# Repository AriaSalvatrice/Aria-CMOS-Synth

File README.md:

# Aria Salvatrice's WIP CMOS Synth

This repository aims to document the Lunetta-style modular CMOS synth I'm building to learn more about electronics. 

Wanna see it in action?

For now, this stuff is only provided publicly to solicit feedback. Depending on the quality of the completed synth and community interest, maybe I'll turn it into a proper open hardware project fit for human consumption one day. But for now, nobody should reproduce those builds, nor even attempt to learn something from them. I literally didn't know how to make a LED emit light rather than smoke at the start of 2022. I have no clue what I'm doing.

Software you need to open the source files I'm sharing:
- Schematics use [KiCad](https://www.kicad.org/) 6.99+
- Layouts use [DIY Layout Creator](http://diy-fever.com/software/diylc/)
- 3D prints use [FreeCAD](https://www.freecadweb.org/)

Other than this file repository, I document my build process [in a thread on the Look Mum No Computer forum](https://lookmumnocomputer.discourse.group/t/starting-a-little-cmos-synth-build/5375/), post the infrequent video [on my Youtube](https://www.youtube.com/c/AriaSalvatrice), sometimes lurk [/r/synthdiy](https://old.reddit.com/r/synthdiy/), and spam [excessively detailed updates in between the gay shitposts on my personal Tweeter that nobody should follow](https://twitter.com/AriaSalvatrice). 

## About Lunetta and CMOS synths

CMOS synths primarily focus primarily on exploring the interactions of the CMOS 4000 series of chips, which deal with digital logic, signals that are either high or low. Compared to more advanced synth DIY endeavors, they are rather easy to build and understand, cheap to make, and reward experimentation. They are sometimes named after [Stanley Lunetta](http://moosack.net/), who pioneered this style of circuit, and called his work _sound sculptures_. 

Your best introduction to musical applications of CMOS chips would be [Elliot Williams' Logic Noise series](https://hackaday.com/series_of_posts/logic-noise/). To dig deeper, explore over a decade of archives in the [Lunetta forums on electro-music.com](https://electro-music.com/forum/forum-160.html), and read the in-depth circuit analyses of the [Castle Rocktronics](http://castlerocktronics.com/modular.html) modules. 

## Design Goals

Mostly learning electronics for myself, and ending up with a neat little rhythm machine, for now. But it'd be cool if I could eventually turn the best circuits into multiple dedicated PCBs, that you could wire up either with pin headers, or cables going to banana jacks on a panel for a more traditional Lunetta setup.

## Electrical Design

All the guts of the synth are exposed as bare PCBs with male header pins, that the performer patches with female DuPont cables. The small size makes it unsuited for live patching, but exceptionally well suited to experimentation with breadboards.

As there are no panels, the aesthetics of the PCBs are important. When performing on video, they must provide a fun and colorful visual spectacle with mucho Blinkenlichten. They must also double as a reasonably ergonomic user interface.

The system runs on +12V DC. It will also work on +9V, but the values are tuned for +12V, so pitches and envelopes are different at +9V. Some of the circuits I made no longer seem to work at +5V. I picked +12V to make it easier to integrate to a modular synth in the future. There is no dedicated power module yet, it runs off a bench PSU.

To keep the patches readable for the performer, most of the hardwiring is run below the boards. 

Most of the circuits used were designed by much more competent people and shared under permissive terms. Individual credits are provided for each module. If you want to learn, learn from the originals, not from my stuff.

## Mechanical Design

The modules are currently printed with PLA. The models were made with FreeCAD. As I don't know FreeCAD well, they are not as easy to modify as I like and can require some post-processing in Blender, the main value of the FreeCAD project is to have a set of measurements that works pretty well. 

The modules tile to an approximate 60×60mm grid. This allows integrating 100×100mm PCBs in 120×120mm modules comfortably, the maximum size for which some PCB fab houses cut you a special deal for minimum quantity orders.

The modules are held together by their feet with little holding rings that look like buttons, taking countersunk screws. The holes in the feet of modules are reinforced with heat set inserts.

The models should not require a particularly well tuned printer to make. Most can be printed without supports and don't require much post-processing.

Here's the main measurements (will add more as I confirm them precisely):

| Dimension Name | Value | Comments |
|----------------|-------|----------|
| Grid size | 60 × 60 mm 
| Height of modules | 18 mm | Tall enough for vertical headers below the boards, but angled are preferred.
| Spacing between modules | 0.8 mm | Currently, 120×120mm modules don't account for this properly.

## Licensing

lol

-----------

Thanxx for peeping my project. Feel free to look at my learning process, but do not treat my schematics and layouts as instructions yielding an usable product.

Send me thoughts and dog gifs to <woof@aria.dog>.

ttyl,

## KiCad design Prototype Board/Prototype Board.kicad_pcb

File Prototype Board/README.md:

Protoboard Rev2B
----------------

Inspired by commercialy available Permanent Prototype boards, and [Analog Output's Protoboard for Eurorack and Kosmo](https://github.com/holmesrichards/Protoboard). It's 99×99 mm, to get the best deal from PCB fab houses.

There's built-in reverse voltage protection, a status LED, a main decoupling capacitor, room for 6 potentiometers or tactile buttons, and two half-breadboard layouts stacked over each other, with power rails.

The footprints at the bottom can be populated with pushbuttons or potentiometers. They are not connected to the rest of the circuit, but the topmost pad of each group can be used to run wires. Bear in mind that potentiometers are mounted with the pins in reverse order.

The 2 groups of 12 pins at the top and 2 groups of 4 pins on the sides are not connected to anything either. Use them creatively, for example for I/O.

The [W], [X], [Y] and [Z] rows are comprised of 6 groups of 5 pads each, which could be useful to run a signal below a chip.

Those boards are for a single rail power supply, limiting their usefulness for most synthesizer projects.

These are the files for Rev2B. Rev2A has been sent to fabricate (will update). Rev2B is the same with a minor correction (misaligned tracks) and has not been tested.

This is a picture of Rev1, which has a few flaws (such as the status LED shorting if populated). It was my first PCB ever, so I'm happy it even worked at all.

------

_This repository documents my learning process. I advise against building those circuits or learning from them. See the [main README file](../README.md) for more information._

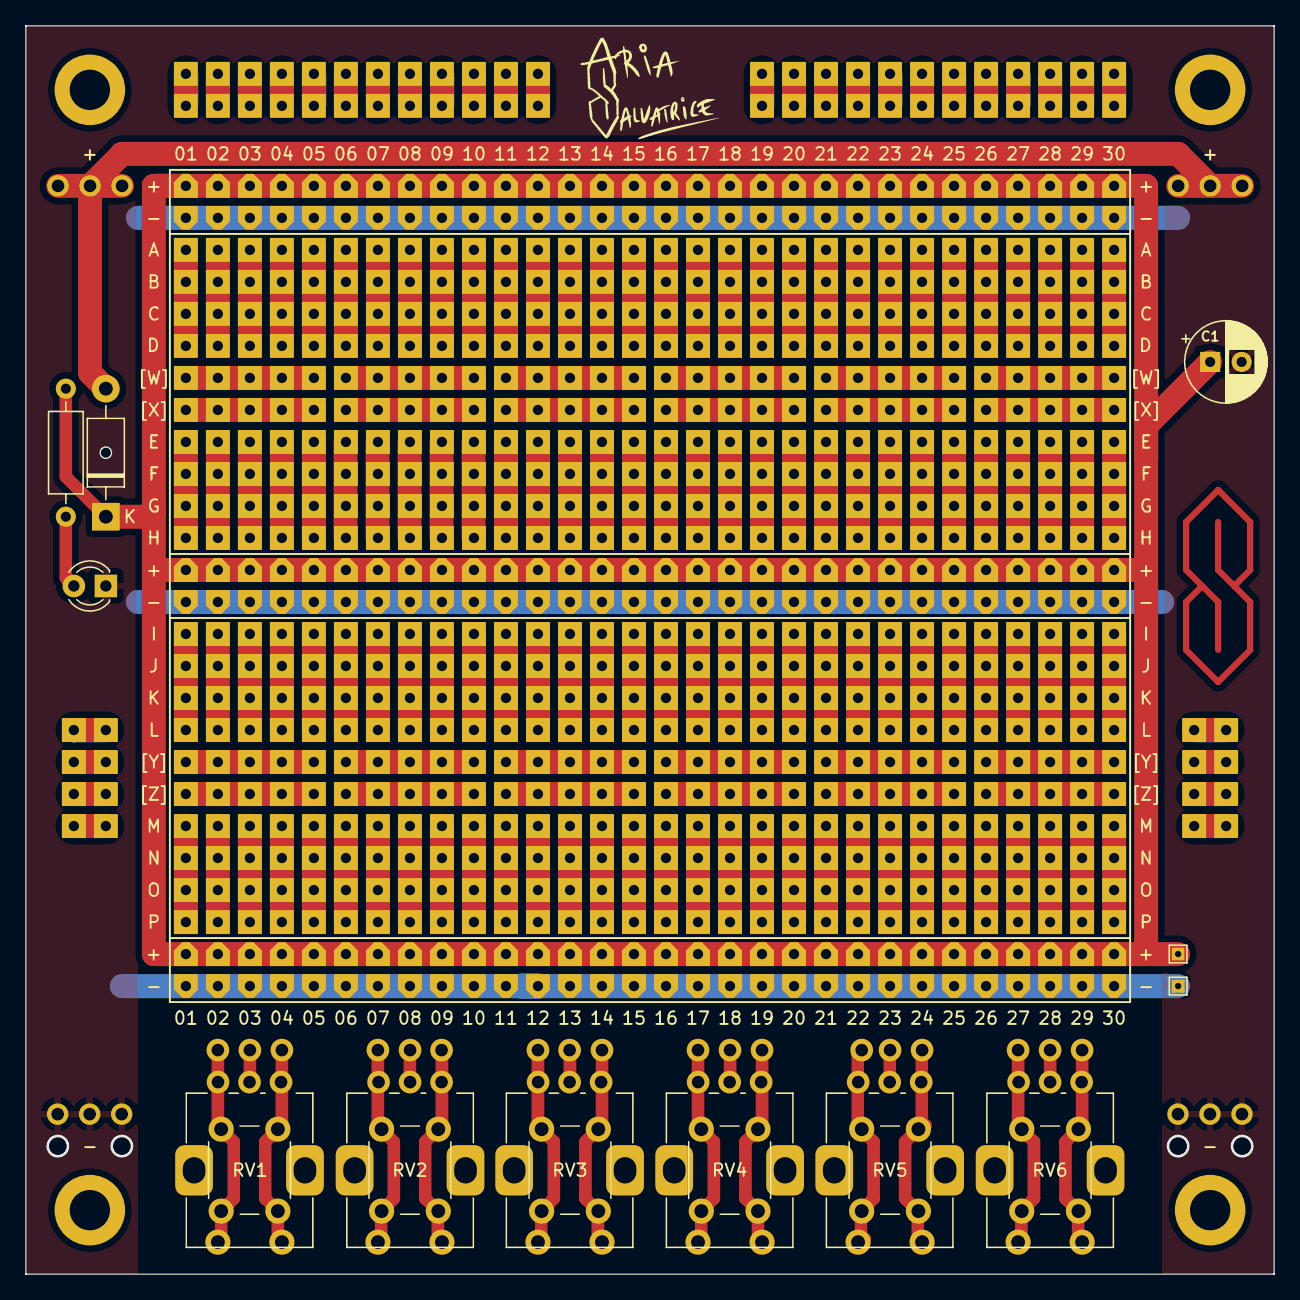
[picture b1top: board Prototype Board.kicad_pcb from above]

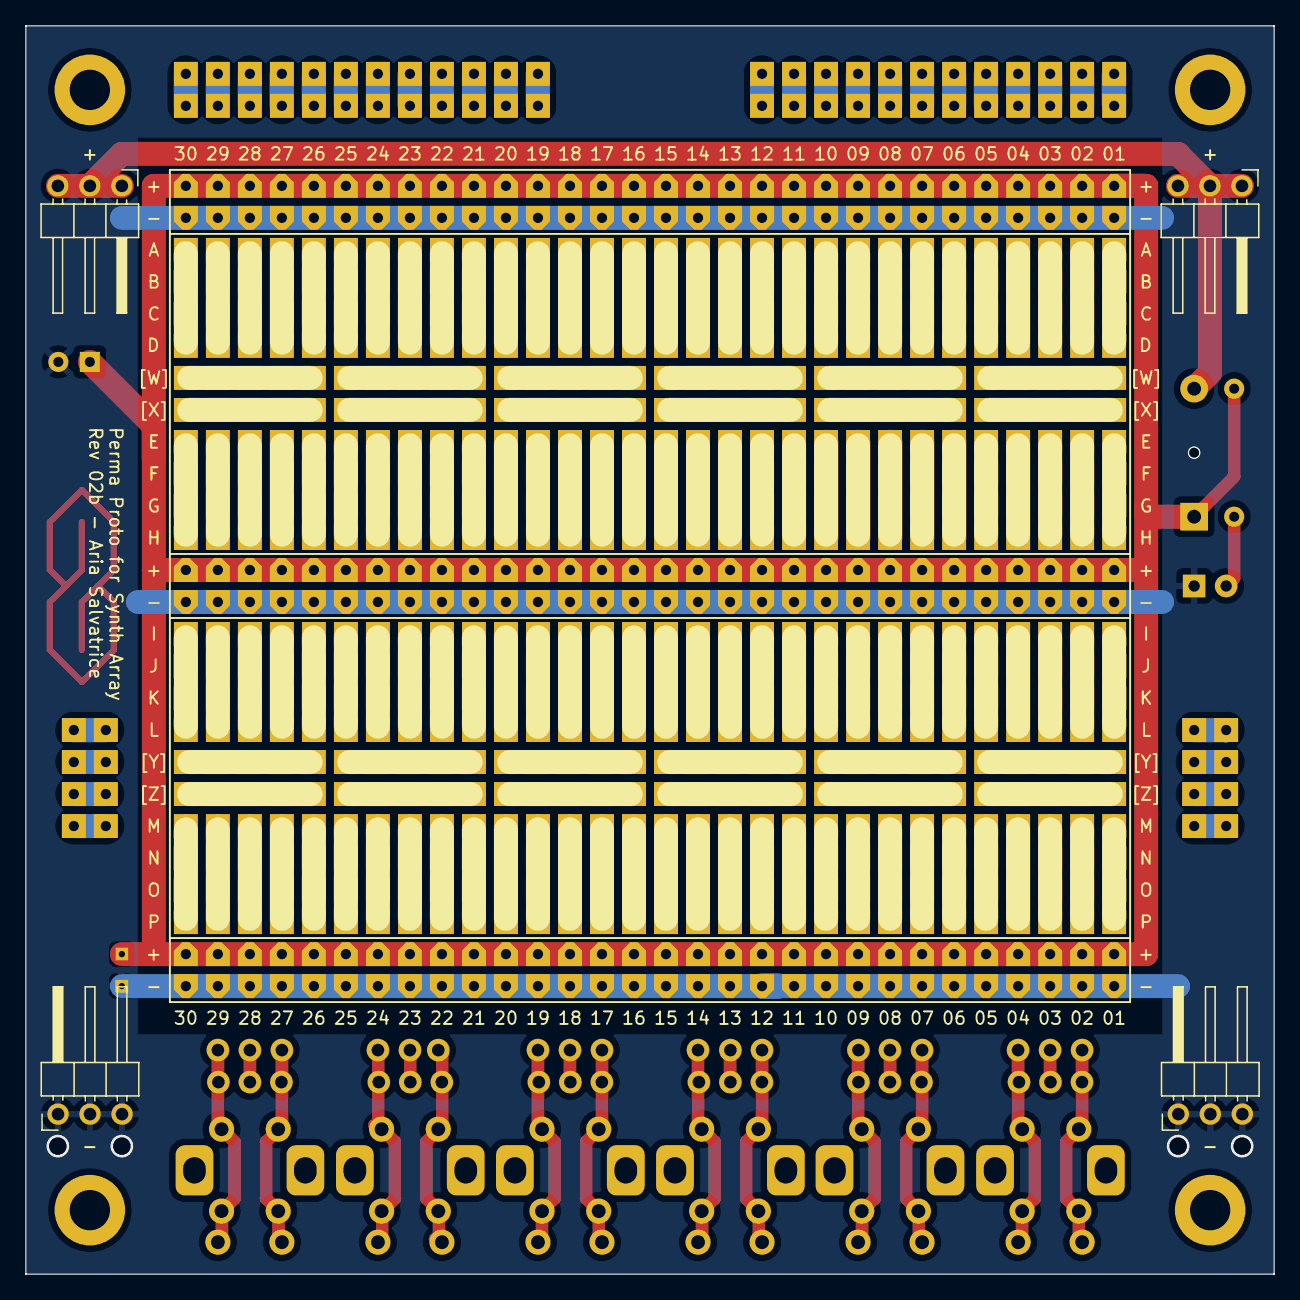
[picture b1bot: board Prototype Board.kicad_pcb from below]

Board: 2 copper layers, 99.1 x 99.1 mm, 219 parts (4 on the bottom side), 22 nets.

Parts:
C1: CP; CP_Radial_D6.3mm_P2.50mm
D1: 1N5817; D_DO-41_SOD81_P10.16mm_Horizontal
D2: LED; LED_D3.0mm
J1, J2, J3, J4, J5, J6, J16, J25, J30, J35, J42, J47, J56, J61, J62, J73, J86, J91, J98, J103, J112, J113, J124, J129, J134, J139, J146, J151, J152, J153, J154, J159: Connectable_Pad_Group_01x02
J7, J8, J9, J10, J17, J18, J19, J20, J21, J22, J23, J24, J26, J27, J28, J29, J31, J32, J33, J34, J36, J37, J38, J39, J43, J44, J45, J46, J48, J49, J50, J51, J52, J53, J54, J55, J57, J58, J59, J60, J63, J64, J65, J66, J69, J70, J71, J72, J74, J75, J76, J77, J78, J79, J80, J81, J82, J83, J84, J85, J87, J88, J89, J90, J94, J95, J96, J97, J99, J100, J101, J102, J104, J105, J106, J107, J108, J109, J110, J111, J114, J115, J116, J117, J120, J121, J122, J123, J125, J126, J127, J128, J130, J131, J132, J133, J135, J136, J137, J138, J140, J141, J142, J143, J147, J148, J149, J150, J155, J156, J157, J158, J160, J161, J162, J163, J164, J165, J166, J167: Connectable_Pad_Group_01x04
J11, J13, J15: Power_Rail_30
J12, J14, J40, J41, J67, J68, J92, J93, J118, J119, J144, J145: Connectable_Pad_Group_02x05
J174, J175, J191, J192: Conn_01x03_Male; PinHeader_1x03_P2.54mm_Horizontal
J176, J177, J178, J179, J180, J181, J182, J183, J184, J185, J186, J187, J188, J189, J190, J199, J200, J201, J202, J203, J204, J205, J206, J207, J208, J209, J210, J211, J212, J213: Conn_01x01; Perf_Board_Hole
R1: 4K7; R_Axial_DIN0207_L6.3mm_D2.5mm_P10.16mm_Horizontal
RV1, RV2, RV3, RV4, RV5, RV6: R_Potentiometer_MountingPin; Potentiometer_Alps_RK09K_Single_Vertical
SW4, SW5, SW6, SW10, SW11, SW12: SW_Push_Dual; SW_PUSH_6mm
TP1, TP2: TestPoint; TestPoint_THTPad_1.0x1.0mm_Drill0.5mm

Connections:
+12V: C1.1, D1.1 (K), J11.1, J13.1, J15.1, R1.2, TP1.1
/12V_Input: D1.2 (A), J174.1, J174.2, J174.3, J191.1, J191.2, J191.3
GND: C1.2, D2.1 (K), J11.2, J13.2, J15.2, J175.1, J175.2, J175.3, J192.1, J192.2, J192.3, TP2.1
unnamed: D2.2 (A), R1.1
unnamed: J176.1, J182.1, RV1.1, SW4.2
unnamed: J177.1, J183.1, RV1.3, SW4.1
unnamed: J178.1, J184.1, RV2.1, SW5.2
unnamed: J179.1, J185.1, RV2.3, SW5.1
unnamed: J180.1, J186.1, RV3.1, SW6.2
unnamed: J181.1, J187.1, RV3.3, SW6.1
unnamed: J188.1, RV1.2
unnamed: J189.1, RV2.2
unnamed: J190.1, RV3.2
unnamed: J199.1, J205.1, RV4.1, SW10.2
unnamed: J200.1, J206.1, RV4.3, SW10.1
unnamed: J201.1, J207.1, RV5.1, SW11.2
unnamed: J202.1, J208.1, RV5.3, SW11.1
unnamed: J203.1, J209.1, RV6.1, SW12.2
unnamed: J204.1, J210.1, RV6.3, SW12.1
unnamed: J211.1, RV4.2
unnamed: J212.1, RV5.2
unnamed: J213.1, RV6.2

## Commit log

2022-10-01 Add the bare minimum info to get started
2022-10-02 More info and pictures
2022-10-02 Speling & clarifications
2022-10-02 More info
2022-10-02 Add 4017 board files
2022-10-02 4017 photo
2022-10-02 +4040 Breakout Board
2022-10-02 Forgot to crop that png
2022-10-02 + 40106 Board
2022-10-02 + Output Module
2022-10-02 + Percussion board
2022-10-02 PDF of Percussions board schematic
2022-10-02 40106 pot type info
2022-10-02 Cropping layout PNGs
2022-10-02 Warning lol
2022-10-03 Adding a few 3D prints
2022-10-03 Move images folder, print readme edit
2022-10-03 Reword main README some
2022-10-03 Explain better what each chip does
2022-10-03 Add *.kicad_prl to gitignore
2022-10-03 Reword main README
2022-10-03 Remove revision from folders
2022-10-03 Add Protoboard project
2022-10-03 Move main README info to Protoboard's
2022-10-03 Protoboard edits
2022-10-03 Readme clarifications
2022-10-03 Improve Protoboard Rev2
2022-10-03 Protoboard Rev2 ready soon, needs checking
2022-10-03 Proto silkscreen adjust, gitignore gerbers
2022-10-04 Standardize prototype board folder name, Rev 2B
2022-10-04 Fix 4017 layout + Speling's
2022-10-05 Remove Rev1 from folder name
2022-10-05 Add new video
2022-10-06 Try out switching sequencer
2022-10-07 Percussions add switching sequencer
2022-10-08 Add switching sequencer to module
2022-10-08 Readme mistake
